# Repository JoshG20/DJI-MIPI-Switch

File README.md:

# DJI-MIPI-Switch
2-Camera Input MIPI Switch for Caddx Vista/DJI Air Unit/Runcam Link systems

## V1.0: Initial Revision (INACTIVE)

- The MIPI Switch has 2 MIPI D-PHY CSI inputs and 1 output, all using the DF56C-26P-0.3V(51) connector standard to the 26P DJI FPV system.
- Switching is performed by the PI3WVR646GEEX analog multiplexer, which is the only device in the video signal path.
- Routing is all length and impedence matched within each connector path. The 3 different connectors have different trace lenghts but this does not matter since each camera just sees a slightly longer or shorter total cable length.
- The selection between A and B cameras is controlled by a Pololu RCS01B, which provides a user adjustable PWM threshhold.
- This PCB has 25.5 x 25.5mm mounting holes to match the Caddx Vista and Runcam Link VTX.
- Note1: This board does not pass through the I2C pins, which means cameras that require configuration will not work. Only 60fps cameras are supported.
- Note2: This board is now INACTIVE. Pinout is incorrect.

## V1.1: Fixes V1.0 issues (FUNCTIONAL, SEE NOTE 2)

- Fixed incorrect assumption that the DJI MIPI Coaxial Cable uses a 1-1 pin configuration. This means that pin 1 on the VTX footprint connects to pin 1 on the Camera. In reality, the cable is a 1-n or 1-26 configuration, which flips the pin numbering on one end. VTX-CAM = one flip, so VTX-PCB-CAM needs 3 to match. Therefore V1.1 has mirrored connector pinouts on the camera output connectors, leading to the correct orientation at all stages.
- Improved the silkscreen labeling on the board, including marking the orientation of the PWM input
- Added 20 x 20 mm mounting holes for flexibility
- Note1: Do not use the pinout in this schematic, it has the MIPI lanes in the wrong order and polarity. It does not affect the function of this board, but only because this chip has interchangeable lanes.
- Note2: This board works, however it does have a bug when switching back and forth rapidly (>1Hz). This crashes the VTX until power cycle.

## V2.0: Integrated PWM reading (TBD)

- Size TBD
- Fixed MIPI lane order and polarity on the connectors.
- Replaces 2.54mm pin header with smaller but still common JST SH1.0
- Replaces Pololu RCS01B with integrated PWM reading circuit TBD
- Blocks rapid switching via TBD
- Stretch goal: I2C handling

# Current Pinout Reference:

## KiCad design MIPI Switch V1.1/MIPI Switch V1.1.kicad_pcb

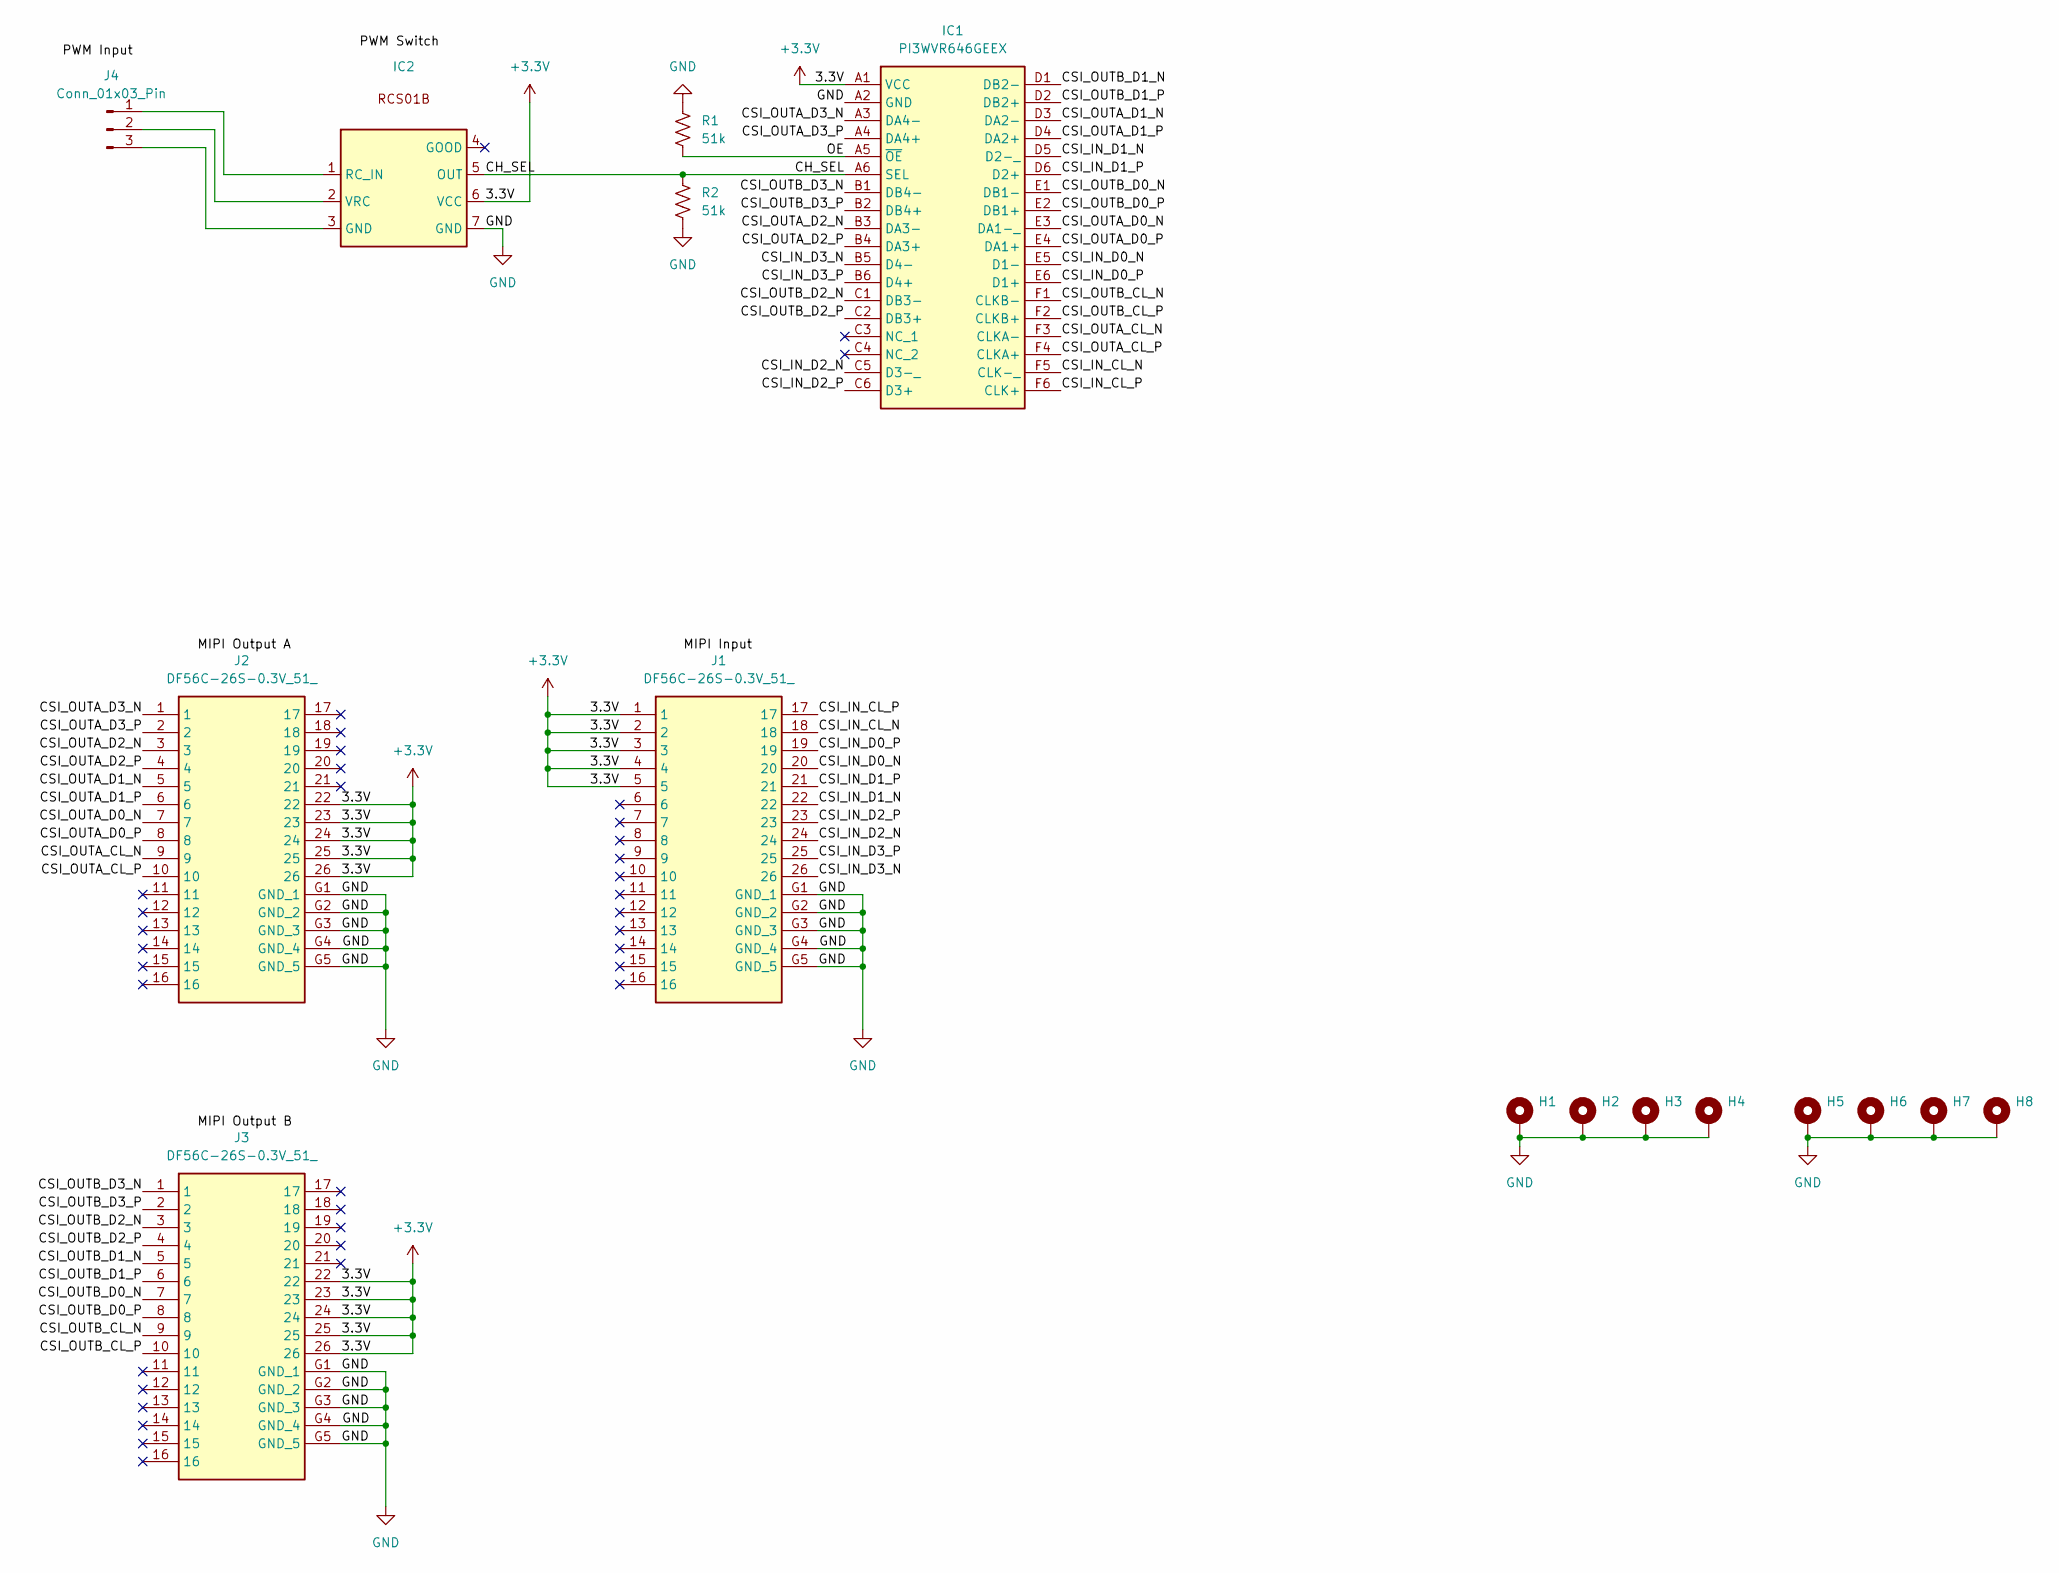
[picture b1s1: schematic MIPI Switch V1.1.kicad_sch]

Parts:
H1, H2, H3, H4, H5, H6, H7, H8: MountingHole_Pad; MountingHole_2.2mm_M2_Pad
IC1: PI3WVR646GEEX; PI3WVR646GEEX_1; Mouser Part Number 729-PI3WVR646GEEX
IC2: RCS01B_PinHeader_2x04_P2.54mm_Vertical
J1, J2, J3: DF56C-26S-0.3V_51_; DF56C26S03V51; Mouser Part Number 798-DF56C-26S-0.3V51
J4: Conn_01x03_Pin; PinHeader_1x03_P2.54mm_Horizontal
R1, R2: 51k; R_0402_1005Metric

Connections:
+3.3V: IC1.A1 (VCC), IC2.6 (VCC), J1.1, J1.2, J1.3, J1.4, J1.5, J2.22, J2.23, J2.24, J2.25, J2.26, J3.22, J3.23, J3.24, J3.25, J3.26
/CH_SEL: IC1.A6 (SEL), IC2.5 (OUT), R2.1
/CSI_IN_CL_N: IC1.F5 (CLK-_), J1.18
/CSI_IN_CL_P: IC1.F6 (CLK+), J1.17
/CSI_IN_D0_N: IC1.E5 (D1-), J1.20
/CSI_IN_D0_P: IC1.E6 (D1+), J1.19
/CSI_IN_D1_N: IC1.D5 (D2-_), J1.22
/CSI_IN_D1_P: IC1.D6 (D2+), J1.21
/CSI_IN_D2_N: IC1.C5 (D3-_), J1.24
/CSI_IN_D2_P: IC1.C6 (D3+), J1.23
/CSI_IN_D3_N: IC1.B5 (D4-), J1.26
/CSI_IN_D3_P: IC1.B6 (D4+), J1.25
/CSI_OUTA_CL_N: IC1.F3 (CLKA-), J2.9
/CSI_OUTA_CL_P: IC1.F4 (CLKA+), J2.10
/CSI_OUTA_D0_N: IC1.E3 (DA1-_), J2.7
/CSI_OUTA_D0_P: IC1.E4 (DA1+), J2.8
/CSI_OUTA_D1_N: IC1.D3 (DA2-), J2.5
/CSI_OUTA_D1_P: IC1.D4 (DA2+), J2.6
/CSI_OUTA_D2_N: IC1.B3 (DA3-), J2.3
/CSI_OUTA_D2_P: IC1.B4 (DA3+), J2.4
/CSI_OUTA_D3_N: IC1.A3 (DA4-), J2.1
/CSI_OUTA_D3_P: IC1.A4 (DA4+), J2.2
/CSI_OUTB_CL_N: IC1.F1 (CLKB-), J3.9
/CSI_OUTB_CL_P: IC1.F2 (CLKB+), J3.10
/CSI_OUTB_D0_N: IC1.E1 (DB1-), J3.7
/CSI_OUTB_D0_P: IC1.E2 (DB1+), J3.8
/CSI_OUTB_D1_N: IC1.D1 (DB2-), J3.5
/CSI_OUTB_D1_P: IC1.D2 (DB2+), J3.6
/CSI_OUTB_D2_N: IC1.C1 (DB3-), J3.3
/CSI_OUTB_D2_P: IC1.C2 (DB3+), J3.4
/CSI_OUTB_D3_N: IC1.B1 (DB4-), J3.1
/CSI_OUTB_D3_P: IC1.B2 (DB4+), J3.2
/OE: IC1.A5 (~OE), R1.2
GND: H1.1, H2.1, H3.1, H4.1, H5.1, H6.1, H7.1, H8.1, IC1.A2 (GND), IC2.7 (GND), J1.G1 (GND_1), J1.G2 (GND_2), J1.G3 (GND_3), J1.G4 (GND_4), J1.G5 (GND_5), J2.G1 (GND_1), J2.G2 (GND_2), J2.G3 (GND_3), J2.G4 (GND_4), J2.G5 (GND_5), J3.G1 (GND_1), J3.G2 (GND_2), J3.G3 (GND_3), J3.G4 (GND_4), J3.G5 (GND_5), R1.1, R2.2
unnamed: IC2.3 (GND), J4.3
unnamed: IC2.1 (RC_IN), J4.1
unnamed: IC2.2 (VRC), J4.2

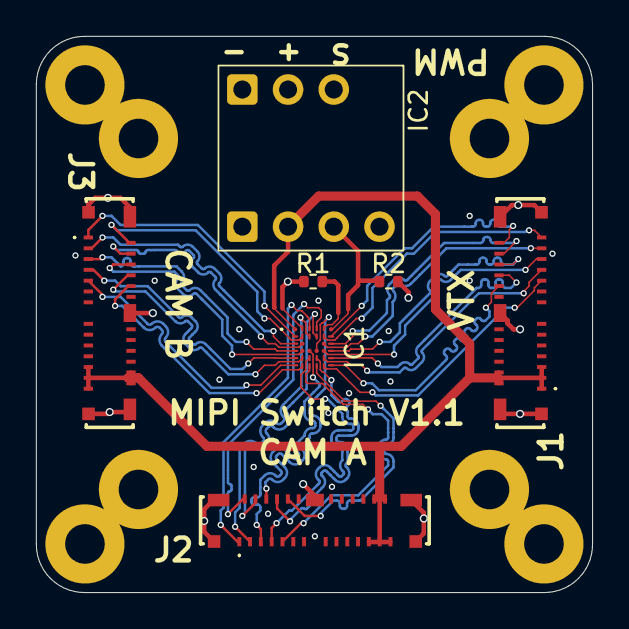
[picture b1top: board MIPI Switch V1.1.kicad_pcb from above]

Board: 4 copper layers, 30.9 x 30.9 mm, 15 parts (0 on the bottom side), 34 nets.

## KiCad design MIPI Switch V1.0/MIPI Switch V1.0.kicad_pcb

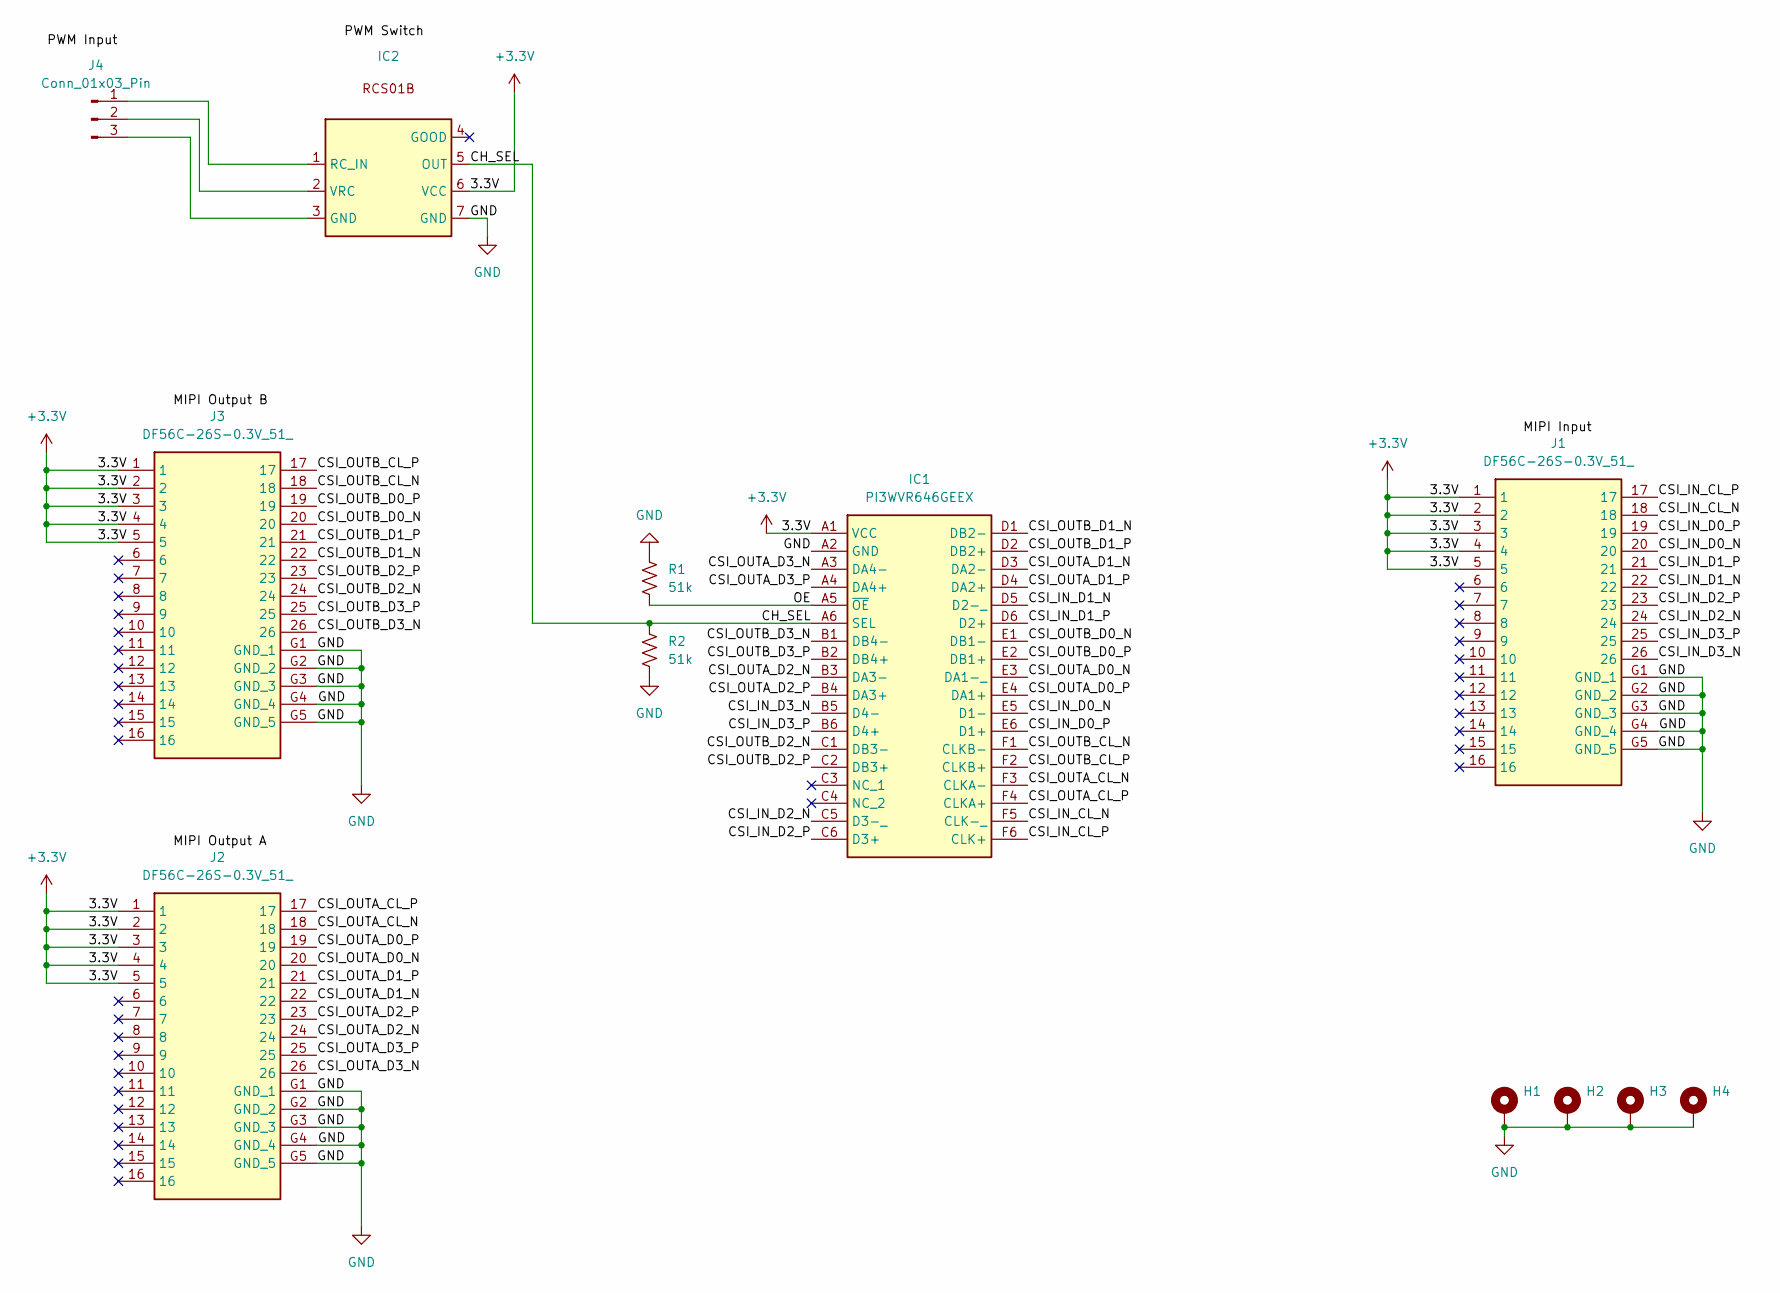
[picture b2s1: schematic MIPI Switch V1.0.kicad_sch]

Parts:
H1, H2, H3, H4: MountingHole_Pad; MountingHole_2.2mm_M2_Pad
IC1: PI3WVR646GEEX; PI3WVR646GEEX_1; Mouser Part Number 729-PI3WVR646GEEX
IC2: RCS01B_PinHeader_2x04_P2.54mm_Vertical
J1, J2, J3: DF56C-26S-0.3V_51_; DF56C26S03V51; Mouser Part Number 798-DF56C-26S-0.3V51
J4: Conn_01x03_Pin; PinHeader_1x03_P2.54mm_Horizontal
R1, R2: 51k; R_0402_1005Metric

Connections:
+3.3V: IC1.A1 (VCC), IC2.6 (VCC), J1.1, J1.2, J1.3, J1.4, J1.5, J2.1, J2.2, J2.3, J2.4, J2.5, J3.1, J3.2, J3.3, J3.4, J3.5
/CH_SEL: IC1.A6 (SEL), IC2.5 (OUT), R2.1
/CSI_IN_CL_N: IC1.F5 (CLK-_), J1.18
/CSI_IN_CL_P: IC1.F6 (CLK+), J1.17
/CSI_IN_D0_N: IC1.E5 (D1-), J1.20
/CSI_IN_D0_P: IC1.E6 (D1+), J1.19
/CSI_IN_D1_N: IC1.D5 (D2-_), J1.22
/CSI_IN_D1_P: IC1.D6 (D2+), J1.21
/CSI_IN_D2_N: IC1.C5 (D3-_), J1.24
/CSI_IN_D2_P: IC1.C6 (D3+), J1.23
/CSI_IN_D3_N: IC1.B5 (D4-), J1.26
/CSI_IN_D3_P: IC1.B6 (D4+), J1.25
/CSI_OUTA_CL_N: IC1.F3 (CLKA-), J2.18
/CSI_OUTA_CL_P: IC1.F4 (CLKA+), J2.17
/CSI_OUTA_D0_N: IC1.E3 (DA1-_), J2.20
/CSI_OUTA_D0_P: IC1.E4 (DA1+), J2.19
/CSI_OUTA_D1_N: IC1.D3 (DA2-), J2.22
/CSI_OUTA_D1_P: IC1.D4 (DA2+), J2.21
/CSI_OUTA_D2_N: IC1.B3 (DA3-), J2.24
/CSI_OUTA_D2_P: IC1.B4 (DA3+), J2.23
/CSI_OUTA_D3_N: IC1.A3 (DA4-), J2.26
/CSI_OUTA_D3_P: IC1.A4 (DA4+), J2.25
/CSI_OUTB_CL_N: IC1.F1 (CLKB-), J3.18
/CSI_OUTB_CL_P: IC1.F2 (CLKB+), J3.17
/CSI_OUTB_D0_N: IC1.E1 (DB1-), J3.20
/CSI_OUTB_D0_P: IC1.E2 (DB1+), J3.19
/CSI_OUTB_D1_N: IC1.D1 (DB2-), J3.22
/CSI_OUTB_D1_P: IC1.D2 (DB2+), J3.21
/CSI_OUTB_D2_N: IC1.C1 (DB3-), J3.24
/CSI_OUTB_D2_P: IC1.C2 (DB3+), J3.23
/CSI_OUTB_D3_N: IC1.B1 (DB4-), J3.26
/CSI_OUTB_D3_P: IC1.B2 (DB4+), J3.25
/OE: IC1.A5 (~OE), R1.2
GND: H1.1, H2.1, H3.1, H4.1, IC1.A2 (GND), IC2.7 (GND), J1.G1 (GND_1), J1.G2 (GND_2), J1.G3 (GND_3), J1.G4 (GND_4), J1.G5 (GND_5), J2.G1 (GND_1), J2.G2 (GND_2), J2.G3 (GND_3), J2.G4 (GND_4), J2.G5 (GND_5), J3.G1 (GND_1), J3.G2 (GND_2), J3.G3 (GND_3), J3.G4 (GND_4), J3.G5 (GND_5), R1.1, R2.2
unnamed: IC2.3 (GND), J4.3
unnamed: IC2.1 (RC_IN), J4.1
unnamed: IC2.2 (VRC), J4.2

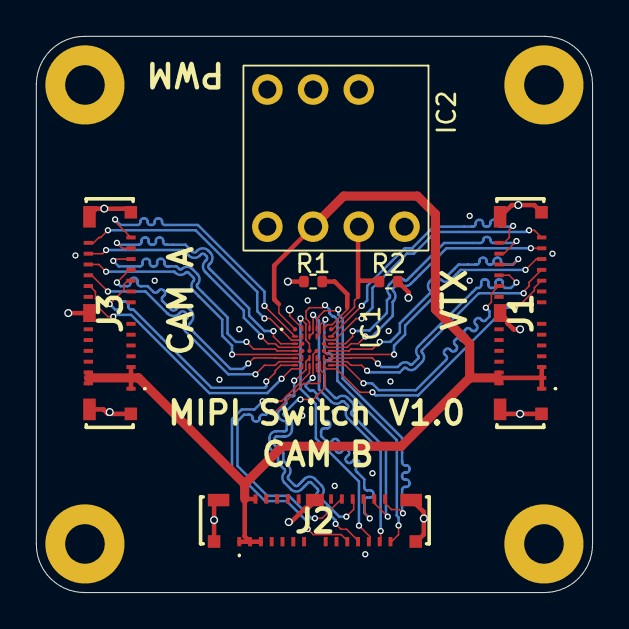
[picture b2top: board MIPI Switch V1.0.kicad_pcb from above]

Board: 4 copper layers, 30.9 x 30.9 mm, 11 parts (0 on the bottom side), 34 nets.

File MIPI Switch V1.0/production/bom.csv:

Designator,Footprint,Quantity,Value,LCSC Part #
IC1,PI3WVR646GEEX_1,1,PI3WVR646GEEX,
"J1, J2, J3",DF56C26S03V51,3,DF56C-26S-0.3V_51_,
"R1, R2",0402,2,50k,

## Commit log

2024-08-17 Initial Upload
2024-08-17 Create LICENSE
2024-08-23 Update README.md
    updated readme to add v1.1 fixes and plan for v2.0
2024-08-23 Delete MIPI Switch V1.0/production directory
    cleanup inactive version
2024-08-23 Delete MIPI Switch V1.0/MIPI Switch V1.0-backups directory
    cleanup inactive version
2024-08-23 Add V1.1 files
2024-08-23 Update README.md
    added current pinout for reference
2024-08-25 Update README.md
    add pictures
2024-08-25 Update README.md
    fixed spaces
2024-08-25 Update README.md
    updated formatting and pinout
2024-08-25 Update README.md
    updated v2.0 changes
2024-08-25 Update README.md
    formatting
2024-08-30 Update README.md
    V1.1 was functional but buggy, update v2.x plans
